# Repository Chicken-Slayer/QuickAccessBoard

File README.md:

# QuickAccessBoard
This is a 12 key macropad that makes use of a rotary encoder and an OLED display. The body was designed in Fusion, and it uses KMK firmware.

## Features:
- 128x32 OLED Display
- EC11 Rotary Encoder
- 12 Keys

## PCB:
Here's the PCB:

## CAD Model:
The case is secured using 4 M3 bolts and heatset inserts. The PCB is held in place in a sandwich arrangement.

It has two separate printed pieces: the base, and the top cover. 

Made in Fusion.

## Firmware Overview
This hackpad uses [KMK](https://github.com/KMKfw/kmk_firmware) firmware for everything. A key matrix is defined in the code, and various macros are assigned to different keys, as well as media control, brightness controls, and setup for an OLED display. The display by default shows a static image, and goes into sleep mode when the keyboard is not in use. 

It can be easily modified to accomodate other macros and the OLED display image can also be easily swapped out for another, or even an animation quite easily.

## BOM:
Here should be everything you need to make this hackpad

- 12x Cherry MX Switches
- 12x DSA Keycaps
- 4x M3x5x4 Heatset inserts
- 4x M3x16mm SHCS Bolts
- 12x 1N4148 DO-35 Diodes.
- 1x 0.91" 128x32 OLED Display
- 1x EC11 Rotary Encoder
- 1x XIAO RP2040
- 1x Case (2 printed parts)

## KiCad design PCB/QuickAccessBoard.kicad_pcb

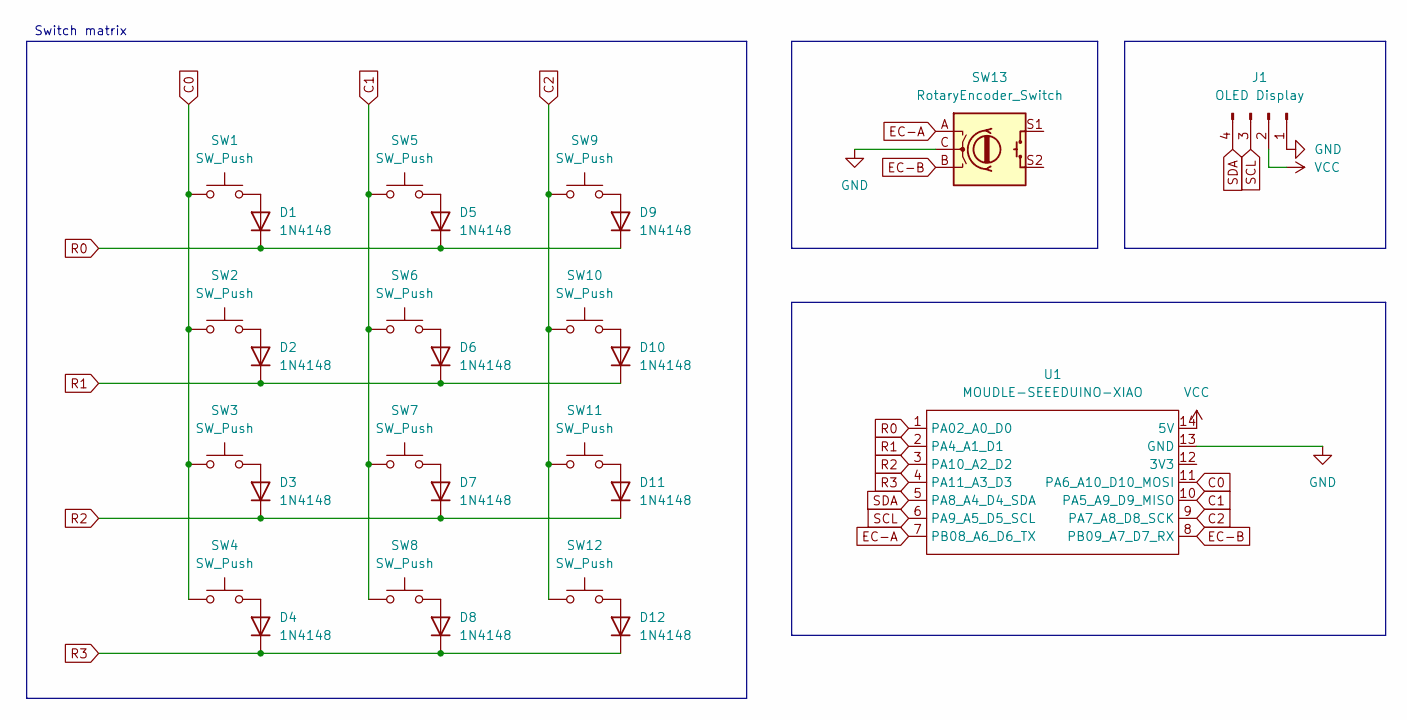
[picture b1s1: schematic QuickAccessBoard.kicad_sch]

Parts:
D1, D2, D3, D4, D5, D6, D7, D8, D9, D10, D11, D12: 1N4148; D_DO-35_SOD27_P7.62mm_Horizontal
J1: OLED Display; SSD1306-0.91-OLED-4pin-128x32
SW1, SW2, SW3, SW4, SW5, SW6, SW7, SW8, SW9, SW10, SW11, SW12: SW_Push; SW_Cherry_MX_1.00u_PCB
SW13: RotaryEncoder_Switch; RotaryEncoder_Alps_EC11E-Switch_Vertical_H20mm
U1: MOUDLE-SEEEDUINO-XIAO; XIAO-Generic-Hybrid-14P-2.54-21X17.8MM

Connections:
C0: SW1.1, SW2.1, SW3.1, SW4.1, U1.11 (PA6_A10_D10_MOSI)
C1: SW5.1, SW6.1, SW7.1, SW8.1, U1.10 (PA5_A9_D9_MISO)
C2: SW9.1, SW10.1, SW11.1, SW12.1, U1.9 (PA7_A8_D8_SCK)
EC-A: SW13.A, U1.7 (PB08_A6_D6_TX)
EC-B: SW13.B, U1.8 (PB09_A7_D7_RX)
GND: J1.1, SW13.C, U1.13 (GND)
unnamed: D1.2 (A), SW1.2
unnamed: D2.2 (A), SW2.2
unnamed: D3.2 (A), SW3.2
unnamed: D4.2 (A), SW4.2
unnamed: D5.2 (A), SW5.2
unnamed: D6.2 (A), SW6.2
unnamed: D7.2 (A), SW7.2
unnamed: D8.2 (A), SW8.2
unnamed: D9.2 (A), SW9.2
unnamed: D10.2 (A), SW10.2
unnamed: D11.2 (A), SW11.2
unnamed: D12.2 (A), SW12.2
R0: D1.1 (K), D5.1 (K), D9.1 (K), U1.1 (PA02_A0_D0)
R1: D2.1 (K), D6.1 (K), D10.1 (K), U1.2 (PA4_A1_D1)
R2: D3.1 (K), D7.1 (K), D11.1 (K), U1.3 (PA10_A2_D2)
R3: D4.1 (K), D8.1 (K), D12.1 (K), U1.4 (PA11_A3_D3)
SCL: J1.3, U1.6 (PA9_A5_D5_SCL)
SDA: J1.4, U1.5 (PA8_A4_D4_SDA)
VCC: J1.2, U1.14 (5V)

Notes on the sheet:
Switch matrix

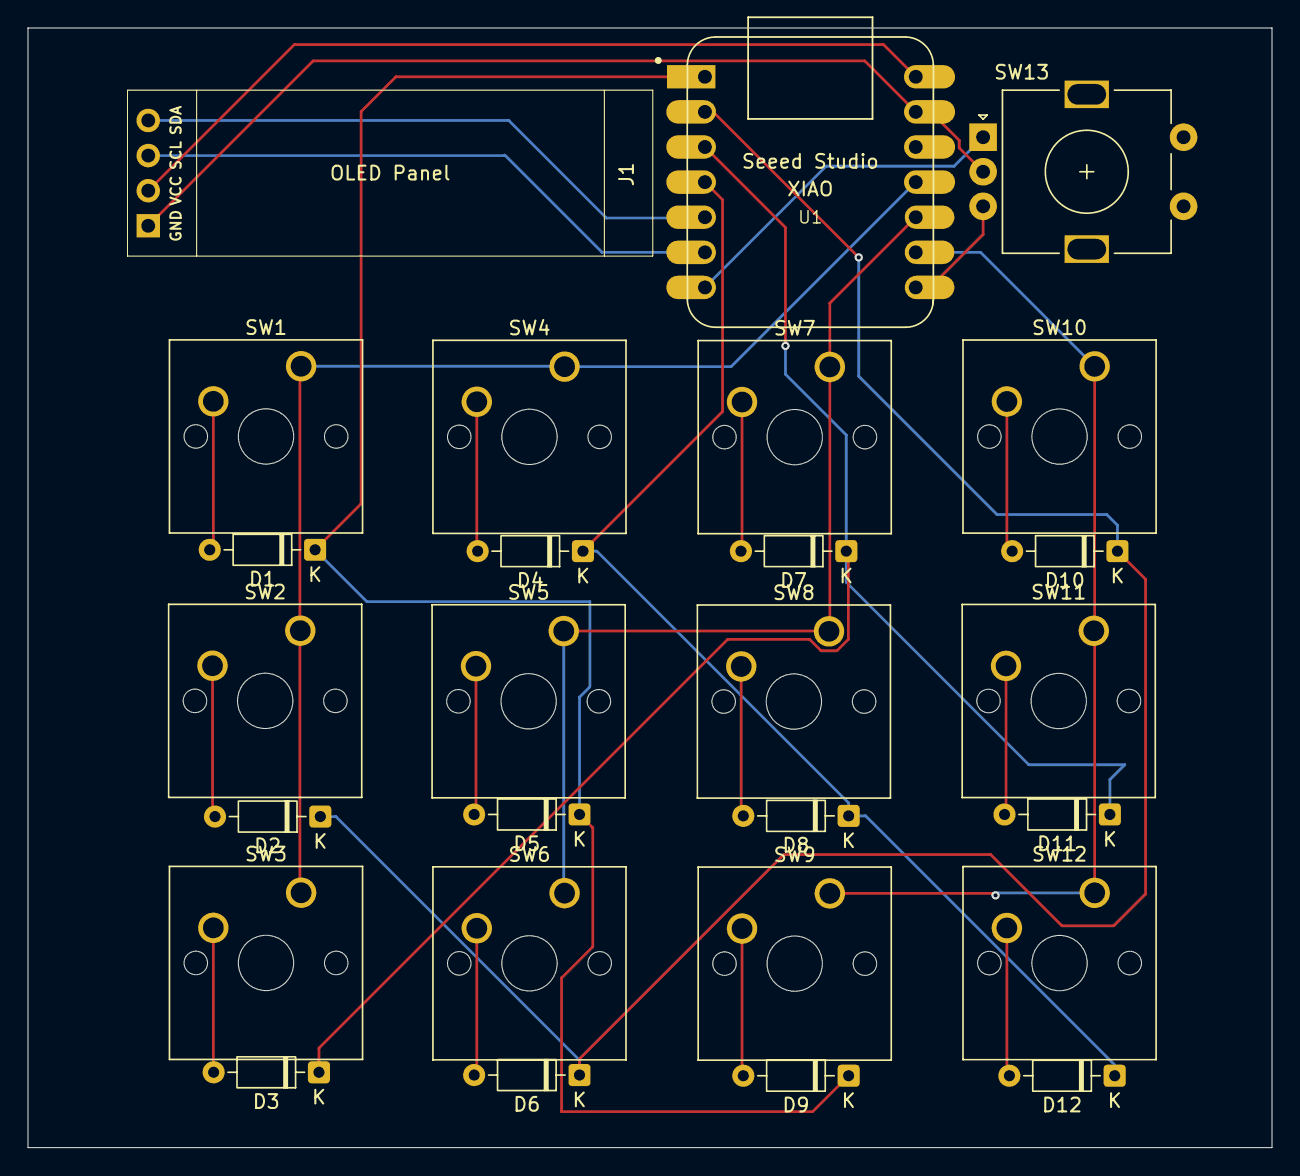
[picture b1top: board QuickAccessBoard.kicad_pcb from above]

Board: 2 copper layers, 90.0 x 81.0 mm, 27 parts (0 on the bottom side), 25 nets.

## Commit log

2026-03-15 Structured Project design files
2026-03-15 Initialised the QMK code
2026-03-15 Finished writing README files
2026-03-15 Added production files
2026-03-15 Fixed flaw in PCB
2026-03-16 Fixed README, added CAD source files
2026-03-21 Fixed gerbers.zip
2026-04-04 Added KMK, put QMK aside
2026-04-13 Updated KMK firmware
2026-04-17 Removed QMK firmware
2026-04-18 Added OLED, rotary encoder functionality
2026-04-21 Fixed code, added module
2026-04-21 Finalised Macros
2026-04-21 Fixed definition
2026-04-23 added cover photo, macro changes
2026-04-23 Removed QMK firmware, update README
